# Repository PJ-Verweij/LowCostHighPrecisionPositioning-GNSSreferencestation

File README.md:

# LowCostHighPrecisionPositioning - GNSSreferencestation

This Github repository contains the manual and production files for the GNSSreferencestation. This design is an improved version of BASE2: [ROVER2 and BASE2 githubpage](https://github.com/PJ-Verweij/LowCostHighPrecisionPositioning---BASE2-ROVER2) <br/><br/>

-In the Documentation folder a manual can be found which explains how to assemble the GNSS reference station <br/>
-In the production files folder the STL file of the antenna top can be found to print the antenna top.
Furthermore, there are Gerber files of the PCB. It is handy to notice that some production facilities also accept the Kicad files. <br/><br/>

-The CAD_model folder can be downloaded an opened with Solidworks (2019 or higher) <br/>
-The PCB folder can be downloaded and opened with KiCad <br/><br/>

-In the Software manuals folder some scripts and instructions are given to demonstrate the functionality of the circuits on the PCB.
For the full Raspberry PI software image and configuration I refer to Andreas Krietemeyer.

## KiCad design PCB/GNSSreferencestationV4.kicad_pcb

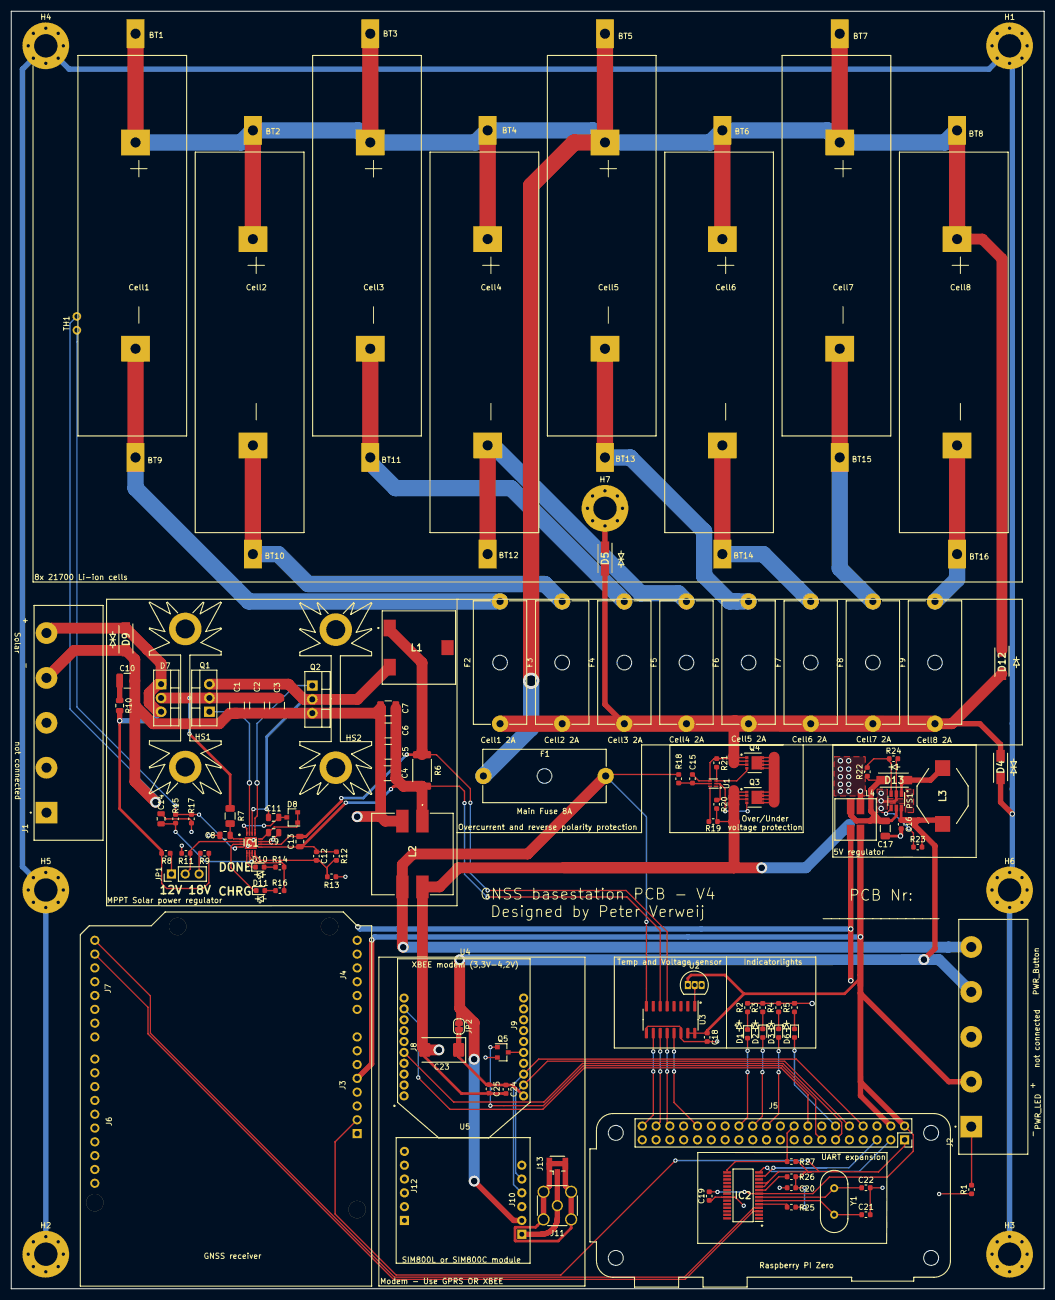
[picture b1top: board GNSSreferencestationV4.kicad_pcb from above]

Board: 2 copper layers, 190.0 x 235.0 mm, 134 parts (0 on the bottom side), 80 nets.

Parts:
BT1, BT2, BT3, BT4, BT5, BT6, BT7, BT8: Battery_Cell; Keystone_246TR_20700
BT9, BT10, BT11, BT12, BT13, BT14, BT15, BT16: Battery_Cell; LocationMarker
C1, C2, C3, C4, C5, C6, C7: 10µ; C_1210_3225Metric
C8, C9, C14: 1µ; C_0805_2012Metric
C10: 2.2µ; C_1210_3225Metric
C11, C13: 0.1µ; C_0805_2012Metric
C12: 22p; C_0603_1608Metric
C15, C18, C19, C20: 0.1µF; C_0603_1608Metric
C16: 10µF; C_0603_1608Metric
C17: 22µF; C_1206_3216Metric
C21: 22pF; C_0603_1608Metric
C22, C25: 33pF; C_0603_1608Metric
C23: 100µF; CP_EIA-7343-30_AVX-N
C24: 10pF; C_0603_1608Metric
D1, D2, D3, D6, D10, D11: LED; LED_0603_1608Metric
D4, D5: SMA6T28CAY; DIOM5126X265N
D7: SBR10U40CT; TO-220-3_Vertical
D8: BAT54C; SOT-23
D9: SMA6T30CAY; DIOM5126X265N
D12, D13: MBRA210LT3G
F1: 8A; Fuseholder_Cylinder-5x20mm_Schurter_0031_8201_Horizontal_Op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
F2, F3, F4, F5, F6, F7, F8, F9: 2A; Fuseholder_Cylinder-5x20mm_Schurter_0031_8201_Horizontal_Op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
H1, H2, H3, H4, H5, H6, H7: Mounthole; MountingHole_4.3mm_M4_Pad_Via
HS1, HS2: Heatsink; Heatsink_Fischer_SK104-STCB_35x13mm__2xDrill3.5mm_ScrewM3
IC1: BQ24650RVAT; QFN50P350X350X100-17N-D
IC2: SC16IS752IPW,128; SOP65P640X110-28N
J1, J2: Conn_01x05_Female; TE_1-1437667-1
J3, J7: Female Header 1x8 pin; LocationMarker
J4, J10, J12: Female Header 1x6 pin; LocationMarker
J5: RPi_header; Raspberry_Pi_Zero_Socketed_THT_FaceDown_MountingHoles
J6: Female Header 1x10 pin; LocationMarker
J8, J9: Female Header 1x10 pin (2mm spacing); LocationMarker
J11: Conn_Coaxial; SMA_Amphenol_132134_Vertical
J13: Conn_Coaxial; U.FL_Hirose_U.FL-R-SMT-1_Vertical
JP1: Jumper_NC_Dual; PinHeader_1x03_P2.54mm_Vertical
JP2: Jumper; SolderJumper-2_P1.3mm_Bridged_RoundedPad1.0x1.5mm
L1: 15µH; SER1390-223MLB
L2: MSD1514-252MED; MSD1514
L3: 2.2µH; DO3316P102MLB
L4: 2.2µH; SRF0703-2R2M
PS1: LTC3426; TSOT-23-6
Q1, Q2: CSD18537NKCS; TO-220-3_Vertical
Q3, Q4: CSD16406Q3; VSON-8_3.3x3.3mm_P0.65mm_NexFET
Q5: DTC143Z; SOT-23
R1: 560; R_0603_1608Metric
R2, R3, R4, R5: 1.5K; R_0603_1608Metric
R6: 0.008; R_2512_6332Metric
R7: 10; R_1206_3216Metric
R8: 324K; R_0603_1608Metric
R9: 511K; R_0603_1608Metric
R10: 2; R_0805_2012Metric
R11: 36K; R_0603_1608Metric
R12: 340K; R_0603_1608Metric
R13: 348K; R_0603_1608Metric
R14, R16: 820; R_0603_1608Metric
R15: 3.48K; R_0603_1608Metric
R17: 14.7K; R_0603_1608Metric
R18: 330; R_0603_1608Metric
R19: 2.2K; R_0603_1608Metric
R20, R21: 5.1M; R_0603_1608Metric
R22: 95.3K; R_0603_1608Metric
R23: 1M; R_0603_1608Metric
R24: 30.9K; R_0603_1608Metric
R25: 10K; R_0603_1608Metric
R26, R27: 1K; R_0603_1608Metric
TH1: 10K; NTCLE100E3103HT1
U1: BQ29700; WSON-6_1.5x1.5mm_P0.5mm
U2: LM35-LP; TO-92L_Inline
U3: MCP3008; SOIC-16_3.9x9.9mm_P1.27mm
U4: Xbee-socket
U5: SIM800module
Y1: 14.7456M; Crystal_HC49-4H_Vertical
simpleRTK2B1: simpleRTK2B_header; simpleRTK2Bheaders_faceup

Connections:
/Batt_0V: C16.2, C17.2, C23.2, C24.2, C25.2, J11.2, J13.2, L2.4, L4.2, PS1.2, Q3.1, Q3.2, Q3.3, Q5.2, R19.2, R20.2, R24.2, U4.10, U5.6
/Batt_VCC: F1.1, J2.5, L2.3, R18.1, U3.8
/Converter_0V: C18.2, C19.1, C20.2, C21.2, C22.2, IC2.22, J5.6, J5.9, J5.14, J5.20, J5.25, J5.30, J5.34, J5.39, L4.4, R1.1, R2.2, R3.2, R4.2, R5.2, U2.3, U3.9, U3.14, simpleRTK2B1.GND1, simpleRTK2B1.GND2, simpleRTK2B1.GND3
/Converter_5V: C18.1, C19.2, IC2.8, J2.2, J5.2, J5.4, L4.3, U2.1, U3.15, U3.16, simpleRTK2B1.5V
/ESD_ground: C15.2, D4.2, D5.2, D12.2, F2.1, F3.1, F4.1, F5.1, F6.1, F7.1, F8.1, F9.1, Q4.1, Q4.2, Q4.3, R21.1, U1.4
/GNSS_RX: IC2.3, simpleRTK2B1.RX1
/GNSS_TX: IC2.4, simpleRTK2B1.TX1
/LED1: D6.2, J5.12
/LED2: D3.2, J5.22
/LED3: D2.2, J5.24
/LED4: D1.2, J5.26
/Modem_RX: J5.8, U4.3, U5.4
/Modem_TX: J5.10, U4.2, U5.5
/Modem_sockets/NET: J11.1, J13.1, U5.1
/Modem_sockets/Powerbutton_VCC: C23.1, C24.1, C25.1, JP2.2, U4.1
/Modem_sockets/Xbee-reset: Q5.3, U4.5
/P_CLK: J5.32, U3.13
/P_CS-SHDN: J5.40, U3.10
/P_Din: J5.38, U3.11
/P_Dout: J5.36, U3.12
/P_IRQ: IC2.15, J5.18, R27.2
/P_SCL: IC2.13, J5.5
/P_SDA: IC2.14, J5.3
/Powerbutton_OUT: C16.1, J2.4, JP2.1, L3.1, PS1.6, R23.2, U5.2
/RPI_3.3V: C20.1, IC2.10, IC2.11, J5.1, R25.2, R26.2, R27.1, simpleRTK2B1.IOREF
/Rpi_Xbee_Reset: J5.13, Q5.1
/Sensors/Temp_SENS: U2.2, U3.1
/Shuntmeasure_high: C13.2, IC1.10, L1.1, R6.2, U3.5
/Shuntmeasure_low: C4.2, C5.2, C6.2, C7.2, C12.1, C13.1, IC1.9, L2.1, R6.1, R12.1, U3.6
/Solarconverter/CHRG: D11.1, IC1.3
/Solarconverter/DONE: D10.1, IC1.5
/Solarconverter/Solar_IN_0V: C1.1, C2.1, C3.1, C4.1, C5.1, C6.1, C7.1, C8.1, C9.1, C10.2, C14.1, D9.2, IC1.11, IC1.17, J1.4, L2.2, Q2.3, R11.2, R13.2, R17.2, TH1.1
/Solarconverter/Solar_IN_VCC: D7.1, D7.3, D9.1, J1.5, R8.1, R9.1, R10.1
/Solarconverter/TERM_EN: C14.2, IC1.6, IC1.7, R14.2, R15.1, R16.2
/Solarconverter/TS: IC1.4, R15.2, R17.1, TH1.2
/Xbee-CTS: J5.16, U4.12
/Xbee-RTS: J5.11, U4.16
unnamed: BT1.1, BT2.1, BT3.1, BT4.1, BT5.1, BT6.1, BT7.1, BT8.1, D12.1, F1.2
unnamed: BT1.2, F2.2
unnamed: BT2.2, F3.2
unnamed: BT3.2, F4.2
unnamed: BT4.2, F5.2
unnamed: BT5.2, F6.2
unnamed: BT6.2, F7.2
unnamed: BT7.2, F8.2
unnamed: BT8.2, F9.2
unnamed: C1.2, C2.2, C3.2, D7.2, Q1.2, R7.1
unnamed: C8.2, IC1.1, R7.2
unnamed: C9.2, D8.1, D8.2, IC1.12
unnamed: C10.1, R10.2
unnamed: C11.1, IC1.14, L1.2, Q1.3, Q2.2
unnamed: C11.2, D8.3, IC1.16
unnamed: C12.2, IC1.8, R12.2, R13.1
unnamed: C15.1, R18.2, U1.5
unnamed: C17.1, D13.1, L4.1, PS1.5, R22.1
unnamed: C21.1, IC2.6, Y1.1
unnamed: C22.1, IC2.7, Y1.2
unnamed: D1.1, R2.1
unnamed: D2.1, R3.1
unnamed: D3.1, R4.1
unnamed: D4.1, H1.1, H2.1, H3.1, H4.1, H5.1, H6.1
unnamed: D5.1, H7.1
unnamed: D6.1, R5.1
unnamed: D10.2, R14.1
unnamed: D11.2, R16.1
unnamed: D13.2, L3.2, PS1.1
unnamed: IC1.2, JP1.2, R11.1
unnamed: IC1.13, Q2.1
unnamed: IC1.15, Q1.1
unnamed: IC2.5, R25.1
unnamed: IC2.9, R26.1
unnamed: J2.1, R1.2
unnamed: JP1.1, R8.2
unnamed: JP1.3, R9.2
unnamed: PS1.3, R22.2, R24.1
unnamed: PS1.4, R23.1
unnamed: Q3.4, R20.1, U1.2
unnamed: Q3.5, Q4.5
unnamed: Q4.4, R21.2, U1.3
unnamed: R19.1, U1.6

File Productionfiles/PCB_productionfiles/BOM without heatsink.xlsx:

Designator | Value | Clarification | Manufacturer | Manufacturer Part Number | Type | Quantity
BT1-BT16 | Battery_Cell | 20700 battery clips | Keystone | 246TR | Thru-Hole | 16
C1-C7 | 10µ | 10µF capacitor | AVX | 12105C106MAT4A | SMD | 7
C8, C9, C14 | 1µ | 1µF capacitor | AVX | 08055C105K4T4A | SMD | 3
C10 | 2.2µ | 2.2µF capacitor | AVX | 12105C225KAZ2A | SMD | 1
C11, C13 | 0.1µ | 0.1µF capacitor | AVX | 08055C104KAT4A | SMD | 2
C12 | 22p | 22pF capacitor | AVX | 06035C220JAT2A | SMD | 1
C15, C18-C20 | 0.1µF | SMD 0.1µF capacitor | AVX | 06035L104K4T4A | SMD | 4
C16 | 10µF | 10µF | AVX | 06033D106MAT2A | SMD | 1
C17 | 22µF | 22µF | AVX | 12063D226KAT2A | SMD | 1
C21 | 22pF | SMD 22pF capacitor | AVX | 06035A220JAT4A | SMD | 1
C22, C25 | 33pF | SMD 33pF capacitor | AVX | 0603YA330F4T2A | SMD | 2
C23 | 100µF | SMD 100µF polarized capacitor | AVX | TCJD107M025R0070E | SMD | 1
C24 | 10pF | SMD 10pF capacitor | AVX | 06035C100K4T4A | SMD | 1
D4, D5 | SMA6T28CAY | ESD protection schottkey diode | STMicroelectronics | SMA6T30CAY | SMD | 2
D1-D3, D6, D10, D11 | LED | SMD RED 2mA LED | Kingbright | APHD1608LSURCK | SMD | 6
D8 | BAT54C | Schottkey diode | Vishay | BAT54C | SMD | 1
D9 | SMA6T30CAY | ESD protection schottkey diode | STMicroelectronics | SMA6T30CAY | SMD | 1
D12, D13 | MBRA210LT3G | Schottkey diode | ON Semiconductor | MBRA210LT3G | SMD | 2
F1 | 8A | 20x5 Fuse holder | Schurter | 318201 | Thru-Hole | 1
F2-F9 | 2A | 20x5 Fuse holder | Schurter | 318201 | Thru-Hole | 8
IC1 | BQ24650RVAT | MPPT solar power converter IC | Texas Instruments | BQ24650RVAT | SMD | 1
IC2 | SC16IS752IPW,128 | I2C to UART IC | NXP | SC16IS752IPW,128 | SMD | 1
J1, J2 | Conn_01x05_Female |  | TE Connectivity / AMP | 4DB-P107-05 | Thru-Hole | 2
J3, J7 | Female Header 1x8 pin |  | Sullins Connector Solutions | PPPC081LFBN-RC | Thru-Hole | 2
J4, J10, J12 | Female Header 1x6 pin |  | Sullins Connector Solutions | PPPC061LFBN-RC | Thru-Hole | 3
J5 | RPi_header |  | Sullins Connector Solutions | PPPC202LFBN-RC | Thru-Hole | 1
J6 | Female Header 1x10 pin |  | Sullins Connector Solutions | PPPC101LFBN-RC | Thru-Hole | 1
J8, J9 | Female Header 1x10 pin (2mm spacing) |  | Sullins Connector Solutions | S5751-10-ND | Thru-Hole | 2
J11 | Conn_Coaxial | Vertical SMA connector | Linx Technologies | CONSMA001-C-G | Thru-Hole | 1
J13 | Conn_Coaxial | U.FL connector | Hirose Connector | U.FL-R-SMT(10) | SMD | 1
JP1 | Jumper_NC_Dual | 1x3 pin header | Amphenol FCI | 10129378-903001BLF | Thru-Hole | 1
L1 | 15µH | 15µH inductor | Coilcraft | SER1390-153MLB | SMD | 1
L2 | MSD1514-252MED | 2.5 µH Coupled-inductor | Coilcraft | MSD1514-252MED | SMD | 1
L3 | 2.2µH | 2.2µH inductor | Coilcraft | D03316P-222 | SMD | 1
L4 | 2.2µH | 2.2µH Coupled-inductor | Bourns | SRF0703-2R2M | SMD | 1
PS1 | LTC3426 | Switching Voltage Regulator | Linear Technology | LTC3426ES6#TRMPBF | SMD | 1
Q3, Q4 | CSD16406Q3 | N-Channel mosfet | Texas Instruments | CSD16406Q3 | SMD | 2
Q5 | DTC143Z | Bipolar transistor pre biased | Nexperia | NHDTC143ZTR | SMD | 1
R1 | 560 | SMD 560Ohm resistor | Vishay | CRCW0603560RFKEAC | SMD | 1
R2-R5 | 1.5K | SMD 1.5K resistor | Vishay | CRCW06031K50FKEAC | SMD | 4
R6 | 0.008 | SMD 0.008Ω current sense resistor | Vishay/Dale | WSLP25128L000FEA | SMD | 1
R7 | 10 | SMD 10Ω resistor | Vishay / Dale | RCS120610R0FKEA | SMD | 1
R8 | 324K | SMD 324K resistor | Vishay / Dale | CRCW0603324KFKEA | SMD | 1
R9 | 511K | SMD 511K resistor | Vishay / Dale | CRCW0603511KFKEA | SMD | 1
R10 | 2 | SMD 2Ω resistor | Vishay / Dale | CRCW08052R00FKEAC | SMD | 1
R11 | 36K | SMD 36K resistor | Vishay / Dale | CRCW060336K0FKEAC | SMD | 1
R12 | 340K | SMD 340K resistor | Vishay/Dale | CRCW0603340KFKEAC | SMD | 1
R13 | 348K | SMD 348K resistor | Vishay/Dale | CRCW0603348KFKEA | SMD | 1
R14, R16 | 820 | SMD 820Ω resistor | Vishay / Dale | CRCW0603820RFKEA | SMD | 2
R15 | 3.48K | SMD 3.48K resistor | Vishay / Dale | CRCW06033K48FKEA | SMD | 1
R17 | 14.7K | SMD 14.7K resistor | Vishay / Dale | CRCW060314K7FKEB | SMD | 1
R18 | 330 | SMD 330ohm resistor | Vishay | CRCW0603330RFKEA | SMD | 1
R19 | 2.2K | SMD 2.2K resistor | Vishay | CRCW06032K20JNEA | SMD | 1
R20, R21 | 5.1M | SMD 5.1M resistor | Vishay | CRCW06035M10FKEA | SMD | 2
R22 | 95.3K | SMD 95.3K resistor | Vishay | CRCW060395K3FKEA | SMD | 1
R23 | 1M | SMD 1M resistor | Vishay | CRCW06031M00FKEB | SMD | 1
R24 | 30.9K | SMD 30.9K resistor | Vishay | CRCW060330K9FKEA | SMD | 1
R25 | 10K | SMD 10K resistor | Vishay | CRCW060310K0FKEAC | SMD | 1
R26, R27 | 1K | SMD 1K resistor | Vishay | CRCW06031K00FKEAC | SMD | 2
TH1 | 10K | 10K NTC Thermistor | Semitec | 103AT-2 | Thru-Hole | 1
U1 | BQ29700 | Battery protection circuit | Texas Instruments | BQ29700DSER | SMD | 1
U2 | LM35-LP | Temperature sensor | Texas Instruments | LM35DZ | Thru-Hole | 1
U3 | MCP3008 | MCP3008 analog-digital converter | Microchip | MCP3008T-I/SL | SMD | 1
Y1 | 14.7456M | 14.7456Mhz crystal | IQD | LFXTAL003224 | Thru-Hole | 1

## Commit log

2021-05-01 Initial upload
2021-05-01 Modem config upload
